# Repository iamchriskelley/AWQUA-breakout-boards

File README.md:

# AWQUA-breakout-boards
A catalog of basic breakout boards, for testing components that will be used in AWQUA water quality monitoring products.

After adding a new board, please update the folder `README.md` with a summary of the component's function and where it can be purchased. Also, please include the datasheet for the component, and match the datasheet and breakout board filename prefixes to the component name.

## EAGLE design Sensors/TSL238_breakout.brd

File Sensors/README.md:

#Sensors

###TSL267
The TSL267 is a high-sensitivity low-noise infrared light-to-voltage converter. It is available at [Mouser](http://www.mouser.com/ProductDetail/ams/TSL26721FN/?qs=%2fha2pyFaduipBcZLiOnOSR43hP6ptMGoi0Q4oZZqVwvdDzgPVlJvvA%3d%3d) and as of this writing costs $1.46/ea (Q10). 

###TSL238
TSL238 is a high-sensitivity light-to-frequency converter. It is available at [Mouser](http://www.mouser.com/ProductDetail/ams/TSL238D-TR/?qs=sGAEpiMZZMsV8lMX1HNLj6sV3N6FJQb0) and as of this writing costs $3.03/ea (Q10).

###TSL230RD
TSL230RD is a high-sensitivity light-to-frequency converter. It is available at [Mouser](http://www.mouser.com/ProductDetail/ams/TSL230RD/?qs=Mty3Fo4ApVjWJHVPSIbomg%3D%3D) and as of this writing costs $3.46/ea (Q10).

###TSL245
TSL245 is a infrared light-to-frequency converter. It is not stocked at [Mouser](http://www.mouser.com/ProductDetail/Texas-Instruments/TSL245/?qs=sGAEpiMZZMvxO7XFMojgsBU15QTW6Nbx). Should call for quote.

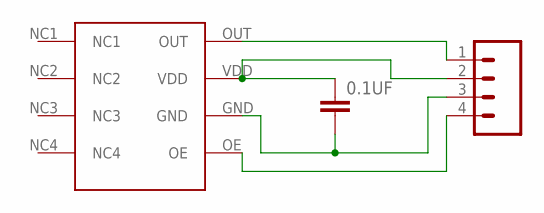
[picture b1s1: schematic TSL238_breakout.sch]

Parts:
0.1UF: CAP0603-CAP; 0603-CAP
J1: M04PTH; 1X04
U$1: TSL238

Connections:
GND: 0.1UF.2, J1.3, U$1.GND
OE: J1.4, U$1.OE
OUT: J1.1, U$1.OUT
VCC: 0.1UF.1, J1.2, U$1.VDD

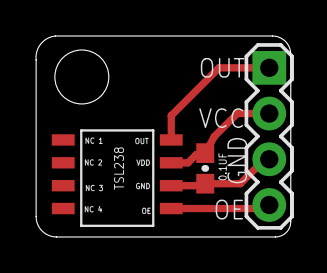
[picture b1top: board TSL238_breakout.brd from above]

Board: 2 copper layers, 14.2 x 11.2 mm, 3 parts (0 on the bottom side), 4 nets.

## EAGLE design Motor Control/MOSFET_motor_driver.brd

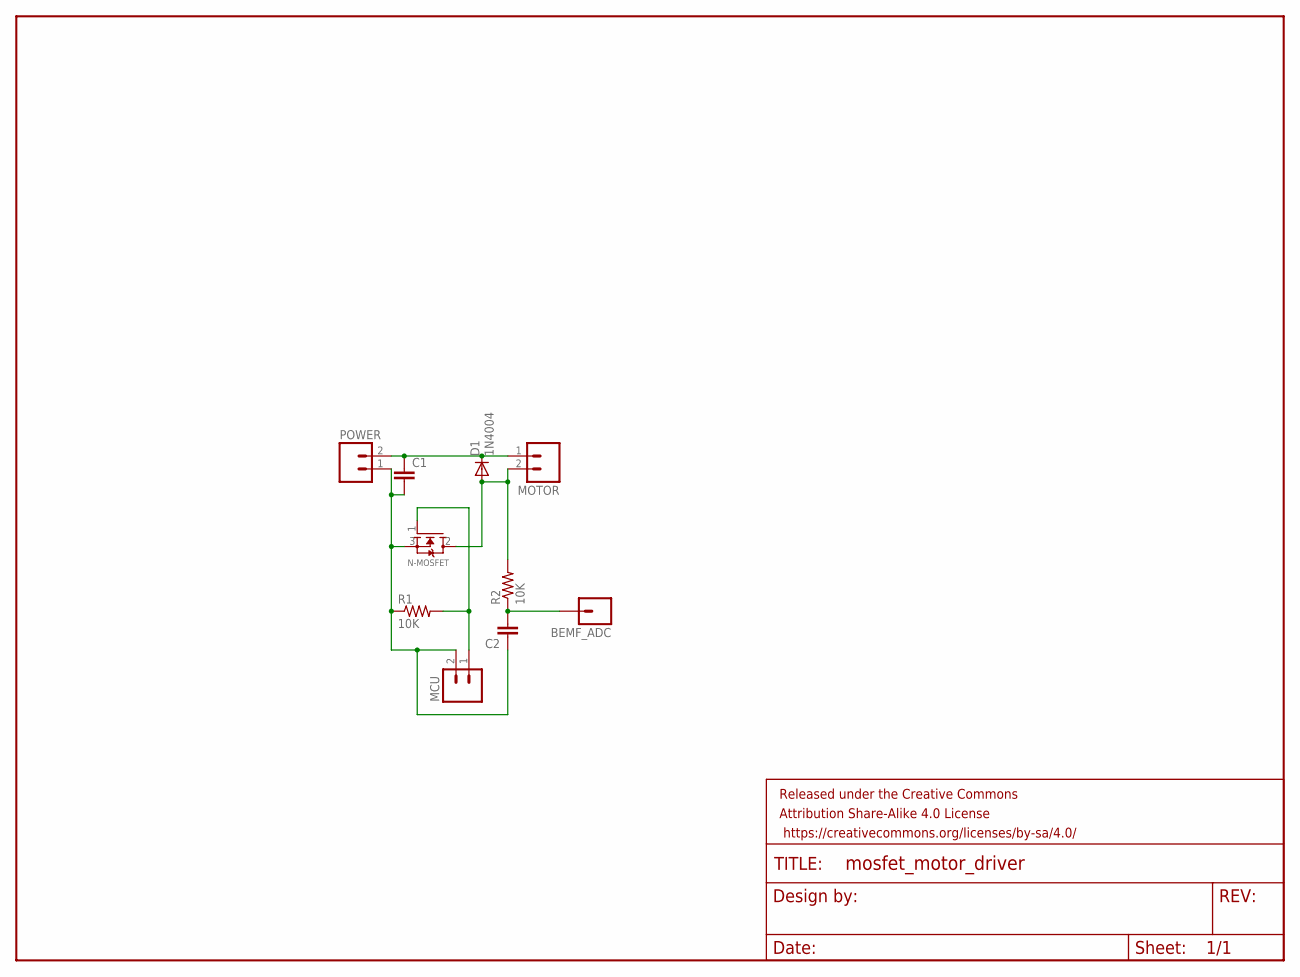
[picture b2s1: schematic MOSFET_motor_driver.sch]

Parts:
BEMF_ADC: M01PTH; 1X01
C1, C2: CAPPTH; CAP-PTH-SMALL
D1: 1N4004; DO41-10
FRAME1: FRAME-LETTER; CREATIVE_COMMONS
MCU: M02PTH; 1X02
MOTOR: M02PTH; 1X02
N-MOSFET: MOSFET-NGDS_TO220V; TO220V
POWER: M02PTH; 1X02
R1, R2: 10K; 0207/10

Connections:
GND: C1.2, C2.1, MCU.2, N-MOSFET.3 (S), POWER.1, R1.1
unnamed: BEMF_ADC.1, C2.2, R2.1
unnamed: MCU.1, N-MOSFET.1 (G), R1.2
unnamed: D1.A, MOTOR.2, N-MOSFET.2 (D), R2.2
unnamed: C1.1, D1.C, MOTOR.1, POWER.2

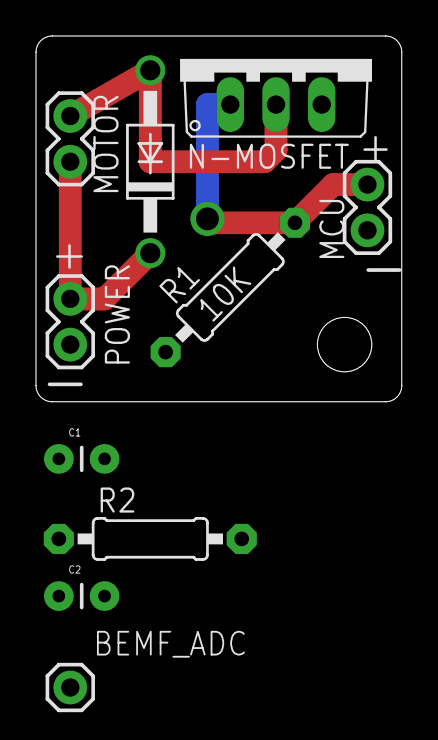
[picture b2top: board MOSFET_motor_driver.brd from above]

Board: 2 copper layers, 20.3 x 20.3 mm, 10 parts (0 on the bottom side), 5 nets.

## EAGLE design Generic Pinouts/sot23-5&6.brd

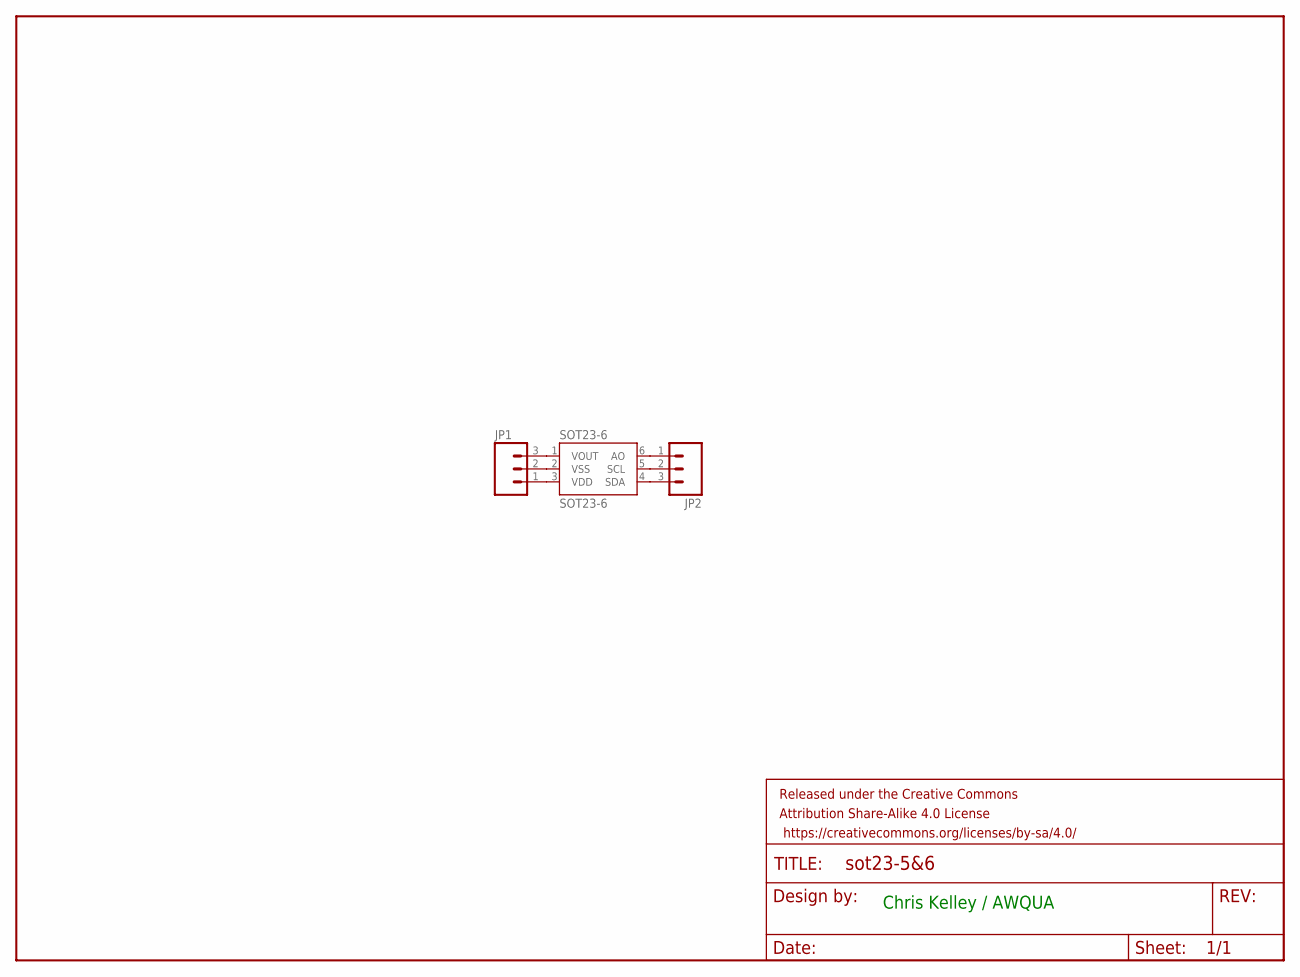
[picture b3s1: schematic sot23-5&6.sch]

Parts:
FRAME1: FRAME-LETTER; CREATIVE_COMMONS
JP1, JP2: M03PTH; 1X03
SOT23-6: SOT23-6

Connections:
unnamed: JP1.1, SOT23-6.3 (VDD)
unnamed: JP1.2, SOT23-6.2 (VSS)
unnamed: JP1.3, SOT23-6.1 (VOUT)
unnamed: JP2.1, SOT23-6.6 (AO)
unnamed: JP2.2, SOT23-6.5 (SCL)
unnamed: JP2.3, SOT23-6.4 (SDA)

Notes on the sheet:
Chris Kelley / AWQUA

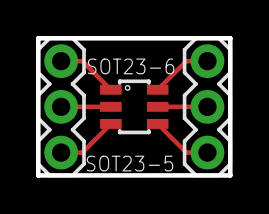
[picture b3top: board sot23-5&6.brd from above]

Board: 2 copper layers, 10.7 x 7.6 mm, 4 parts (0 on the bottom side), 6 nets.

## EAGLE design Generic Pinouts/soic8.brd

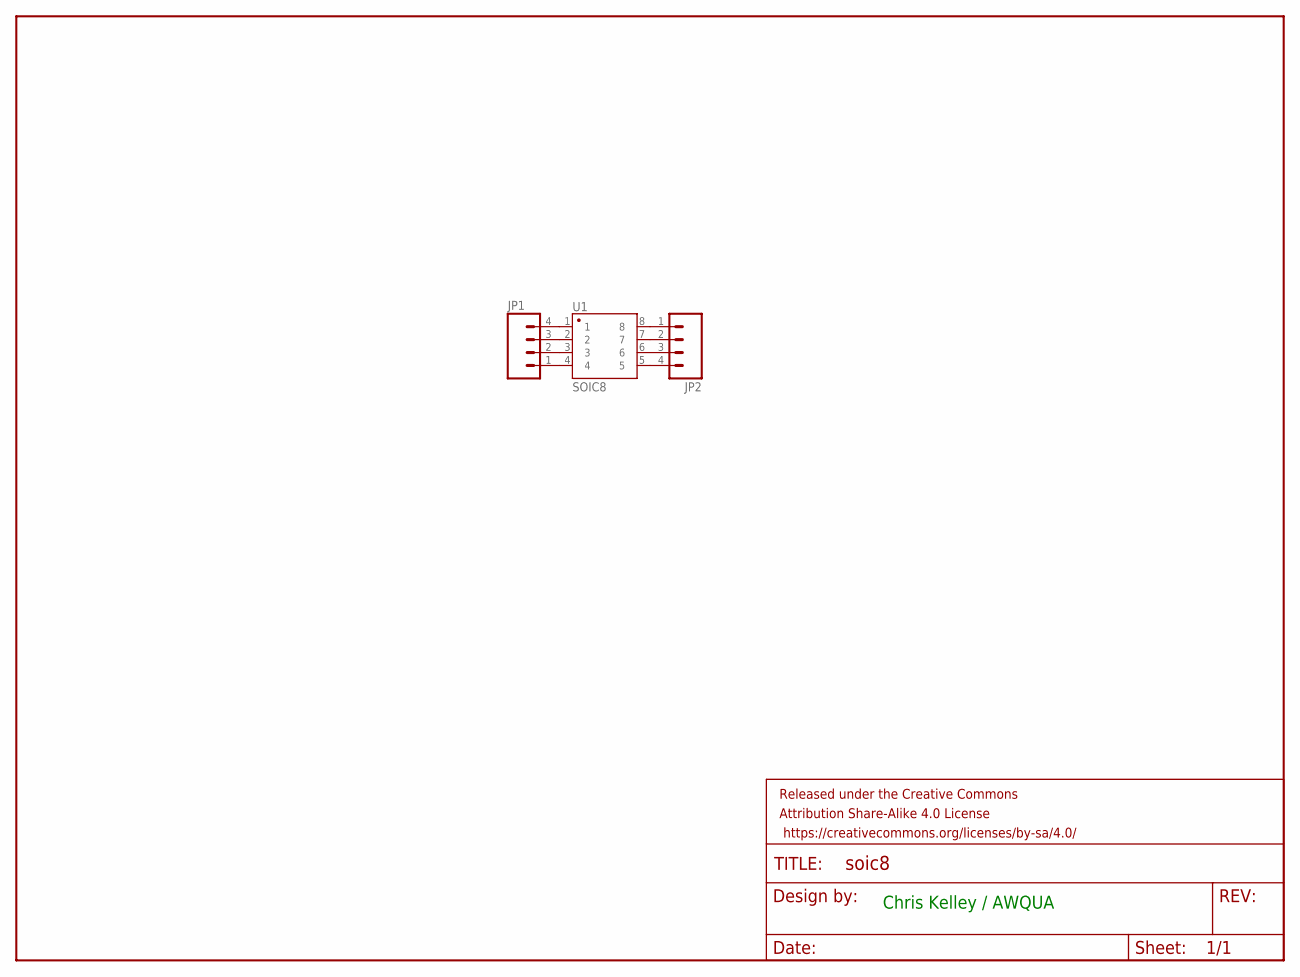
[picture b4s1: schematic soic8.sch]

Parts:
FRAME1: FRAME-LETTER; CREATIVE_COMMONS
JP1, JP2: M04PTH; 1X04
U1: SOIC8; SO08-UNIVERSAL

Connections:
unnamed: JP1.1, U1.4
unnamed: JP1.2, U1.3
unnamed: JP1.3, U1.2
unnamed: JP1.4, U1.1
unnamed: JP2.1, U1.8
unnamed: JP2.2, U1.7
unnamed: JP2.3, U1.6
unnamed: JP2.4, U1.5

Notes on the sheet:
Chris Kelley / AWQUA

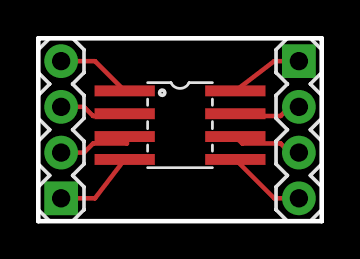
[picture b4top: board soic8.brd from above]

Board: 2 copper layers, 15.7 x 10.2 mm, 4 parts (0 on the bottom side), 8 nets.

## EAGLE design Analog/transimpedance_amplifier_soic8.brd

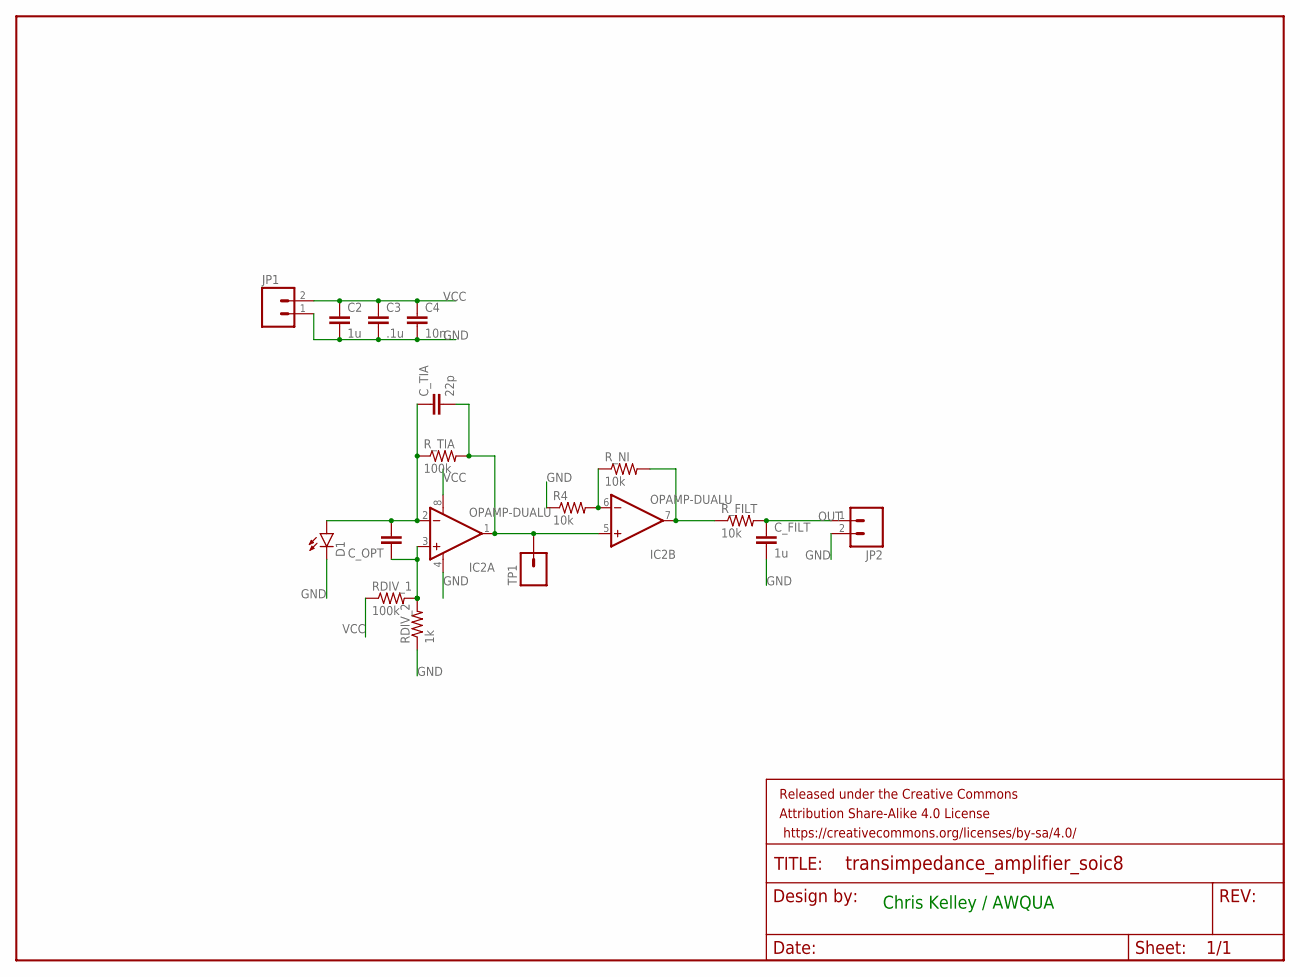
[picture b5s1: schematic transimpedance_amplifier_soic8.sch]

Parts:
C2: 1u; 0805
C3: .1u; 0805
C4: 10n; 0805
C_FILT: 1u; 0805
C_OPT: CAP0805; 0805
C_TIA: 22p; 0805
D1: LED5MM
FRAME1: FRAME-LETTER; CREATIVE_COMMONS
IC2: OPAMP-DUALU; SO08
JP1, JP2: M02PTH; 1X02
R4: 10k; 0603-RES
RDIV_1: 100k; 0603-RES
RDIV_2: 1k; 0603-RES
R_FILT: 10k; 0603-RES
R_NI: 10k; 0603-RES
R_TIA: 100k; 0603-RES
TP1: M01PTH; 1X01

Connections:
GND: C2.2, C3.2, C4.2, C_FILT.2, D1.K (C), IC2.4 (V-), JP1.1, JP2.2, R4.1, RDIV_2.1
unnamed: C_OPT.2, C_TIA.1, D1.A, IC2.2 (-IN), R_TIA.1
unnamed: C_TIA.2, IC2.1 (OUT), IC2.5 (+IN), R_TIA.2, TP1.1
unnamed: C_OPT.1, IC2.3 (+IN), RDIV_1.2, RDIV_2.2
unnamed: IC2.7 (OUT), R_FILT.1, R_NI.2
unnamed: IC2.6 (-IN), R4.2, R_NI.1
OUT: C_FILT.1, JP2.1, R_FILT.2
VCC: C2.1, C3.1, C4.1, IC2.8 (V+), JP1.2, RDIV_1.1

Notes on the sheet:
Chris Kelley / AWQUA

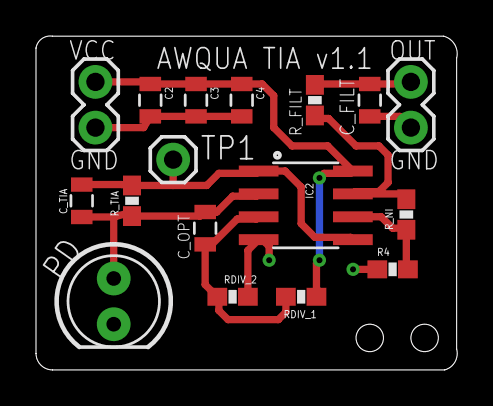
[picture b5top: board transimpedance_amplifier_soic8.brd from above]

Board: 2 copper layers, 23.4 x 18.6 mm, 18 parts (0 on the bottom side), 8 nets.

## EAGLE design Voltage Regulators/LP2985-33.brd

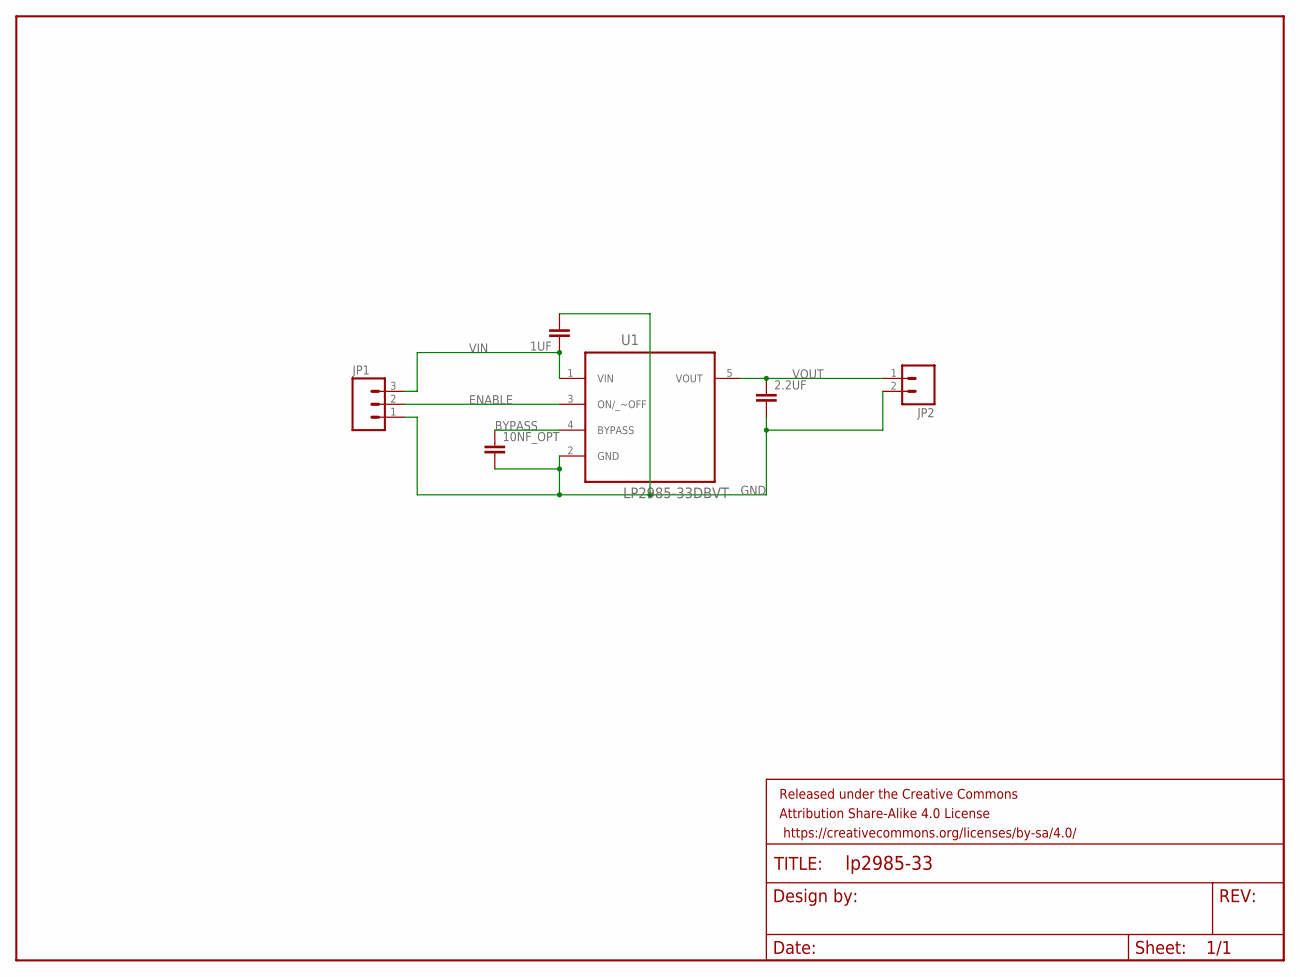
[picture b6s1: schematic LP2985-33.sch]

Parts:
1UF, 2.2UF, 10NF_OPT: CAP0603-CAP; 0603-CAP
FRAME1: FRAME-LETTER; CREATIVE_COMMONS
JP1: M03PTH; 1X03
JP2: M02PTH; 1X02
U1: LP2985-33DBVT; SOT95P280X145-5N

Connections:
BYPASS: 10NF_OPT.1, U1.4 (BYPASS)
ENABLE: JP1.2, U1.3 (ON/_~OFF)
GND: 1UF.2, 2.2UF.2, 10NF_OPT.2, JP1.1, JP2.2, U1.2 (GND)
VIN: 1UF.1, JP1.3, U1.1 (VIN)
VOUT: 2.2UF.1, JP2.1, U1.5 (VOUT)

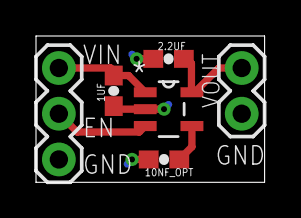
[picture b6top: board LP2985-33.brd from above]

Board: 2 copper layers, 12.7 x 8.1 mm, 7 parts (0 on the bottom side), 5 nets.

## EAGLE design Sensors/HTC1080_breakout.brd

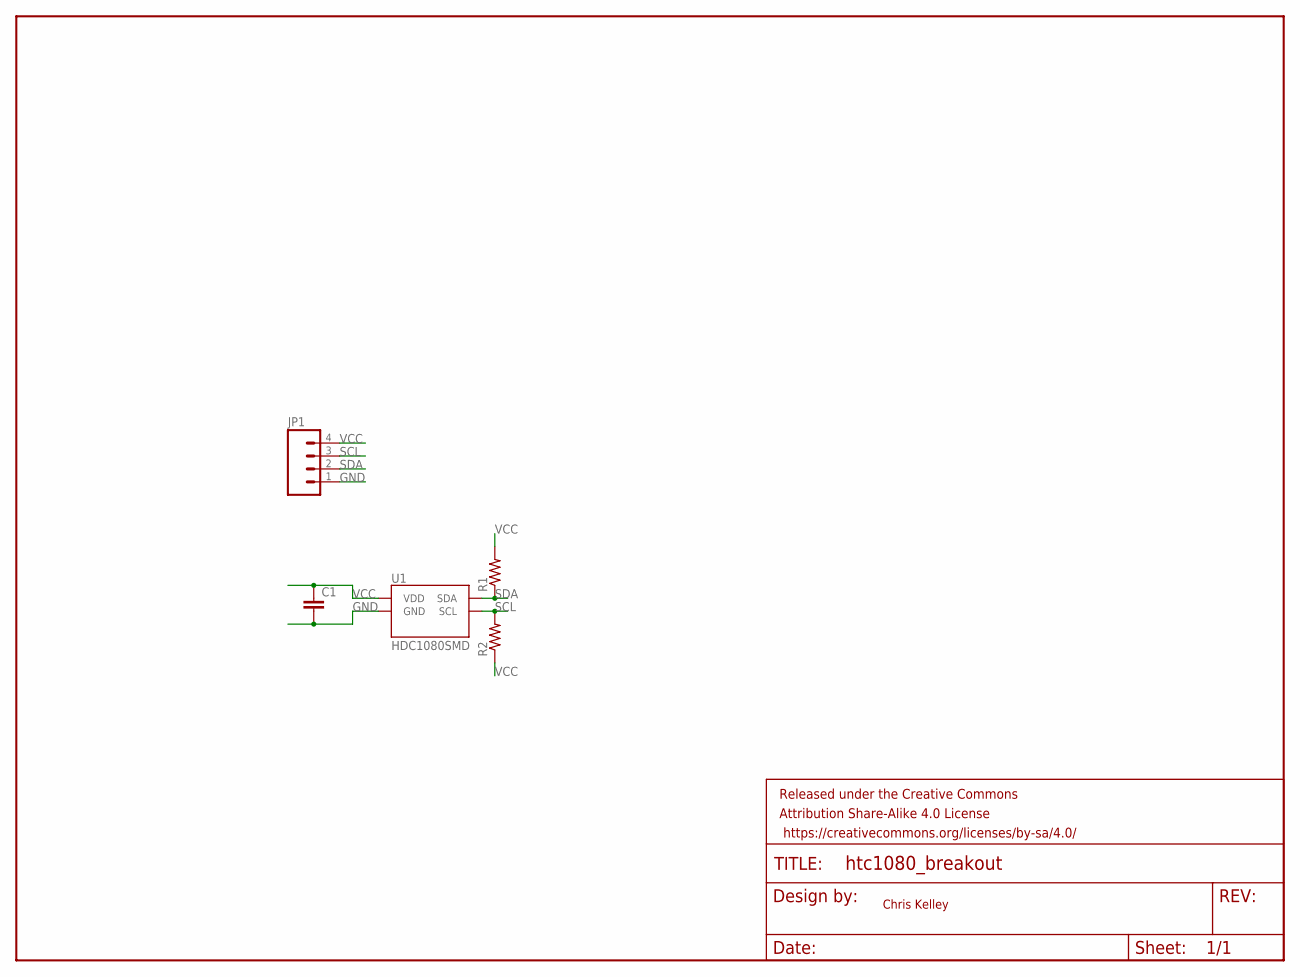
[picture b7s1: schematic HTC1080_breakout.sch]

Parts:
C1: CAP0603-CAP; 0603-CAP
FRAME1: FRAME-LETTER; CREATIVE_COMMONS
JP1: M04PTH; 1X04
R1, R2: RESISTOR0603-RES; 0603-RES
U1: HDC1080SMD; TI-PWSON6-DMB

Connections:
GND: C1.2, JP1.1, U1.GND
SCL: JP1.3, R2.2, U1.SCL
SDA: JP1.2, R1.1, U1.SDA
VCC: C1.1, JP1.4, R1.2, R2.1, U1.VDD

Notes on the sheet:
Chris Kelley

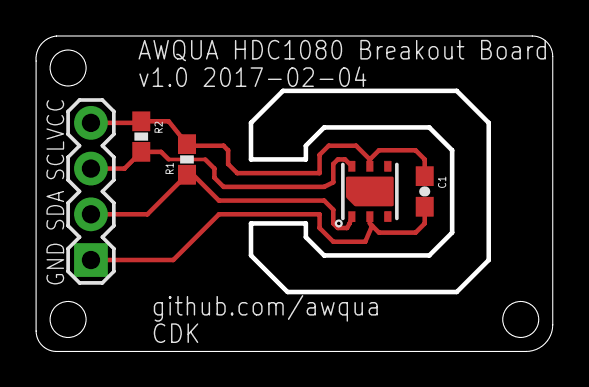
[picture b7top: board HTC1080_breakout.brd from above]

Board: 2 copper layers, 28.7 x 17.5 mm, 6 parts (0 on the bottom side), 4 nets.

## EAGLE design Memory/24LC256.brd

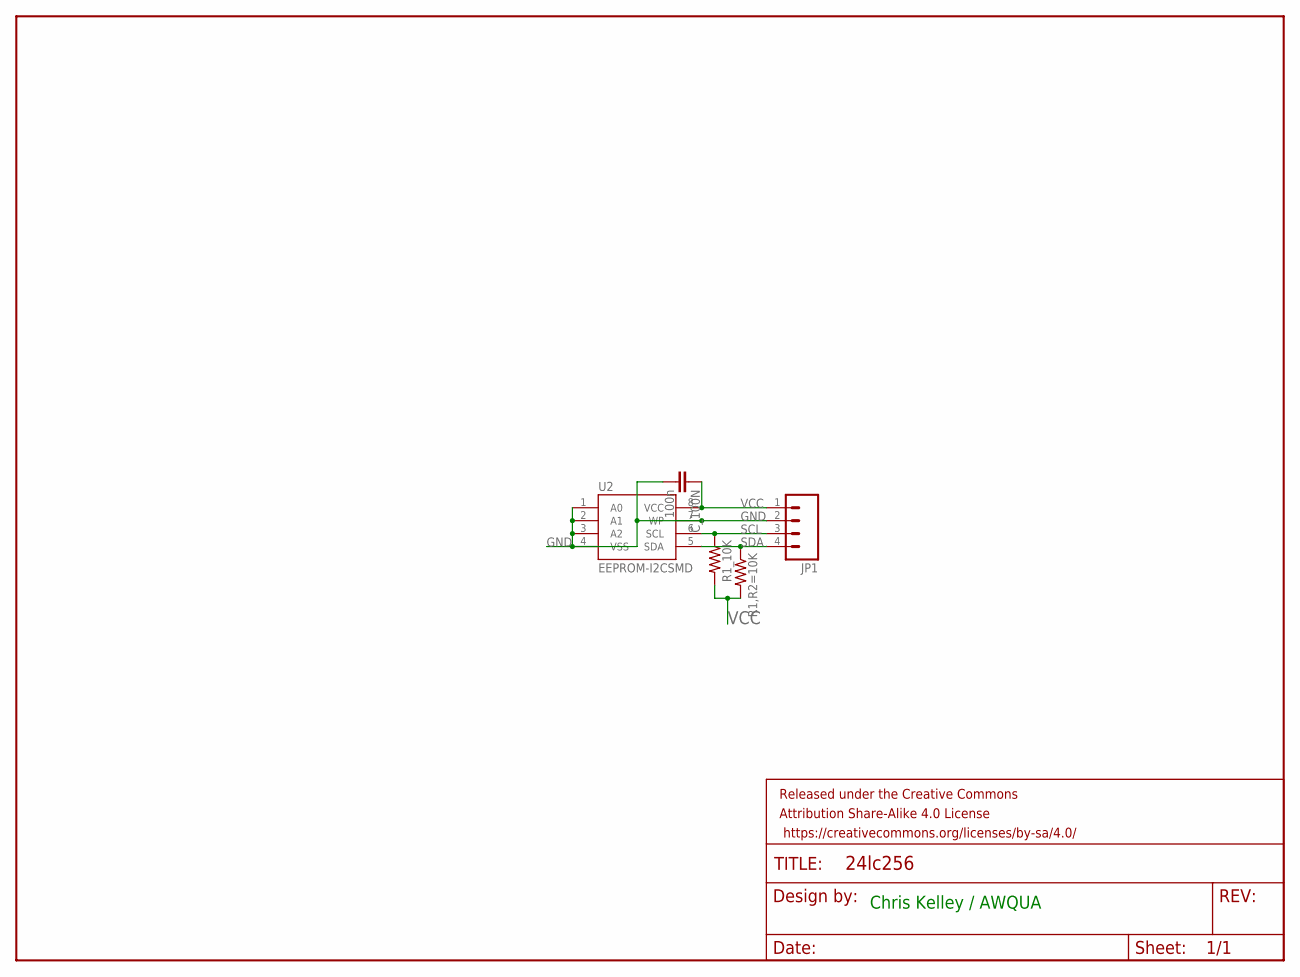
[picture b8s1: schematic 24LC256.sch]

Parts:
C_100N: 100n; 0603-CAP
FRAME1: FRAME-LETTER; CREATIVE_COMMONS
JP1: M04PTH; 1X04
R1,R2=10K, R1_10K: RESISTOR0603-RES; 0603-RES
U2: EEPROM-I2CSMD; SO08

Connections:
GND: C_100N.2, JP1.2, U2.1 (A0), U2.2 (A1), U2.3 (A2), U2.4 (VSS), U2.7 (WP)
SCL: JP1.3, R1_10K.1, U2.6 (SCL)
SDA: JP1.4, R1,R2=10K.1, U2.5 (SDA)
VCC: C_100N.1, JP1.1, R1,R2=10K.2, R1_10K.2, U2.8 (VCC)

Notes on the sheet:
Chris Kelley / AWQUA

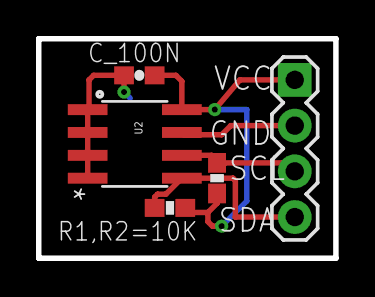
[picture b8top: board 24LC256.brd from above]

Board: 2 copper layers, 16.5 x 12.2 mm, 6 parts (0 on the bottom side), 4 nets.

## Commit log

2016-02-24 adding sensors folder
2016-02-24 added TSL267 breakout board
2016-02-24 increased pogo pin hole size in icsp header
2016-02-24 created TSL238 scheme and board (device not built yet)
2016-02-24 updating readme
2016-02-25 Added tsl230RD breakout and datasheet
2016-02-29 Updated TSL238
2016-02-29 Created TSL breakout boards
2017-01-15 eagle version update
2017-03-06 new boards
2018-07-12 library update

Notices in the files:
parts and their libraries:
SparkFun-Passives: Licensing: Creative Commons ShareAlike 4.0 International - https://creativecommons.org/licenses/by-sa/4.0
SparkFun-Aesthetics: Released under the Creative Commons Attribution Share-Alike 4.0 License
SparkFun-Aesthetics: https://creativecommons.org/licenses/by-sa/4.0
